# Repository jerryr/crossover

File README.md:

## Active Audio crossover
This circuit is based on https://sound-au.com/project09.htm

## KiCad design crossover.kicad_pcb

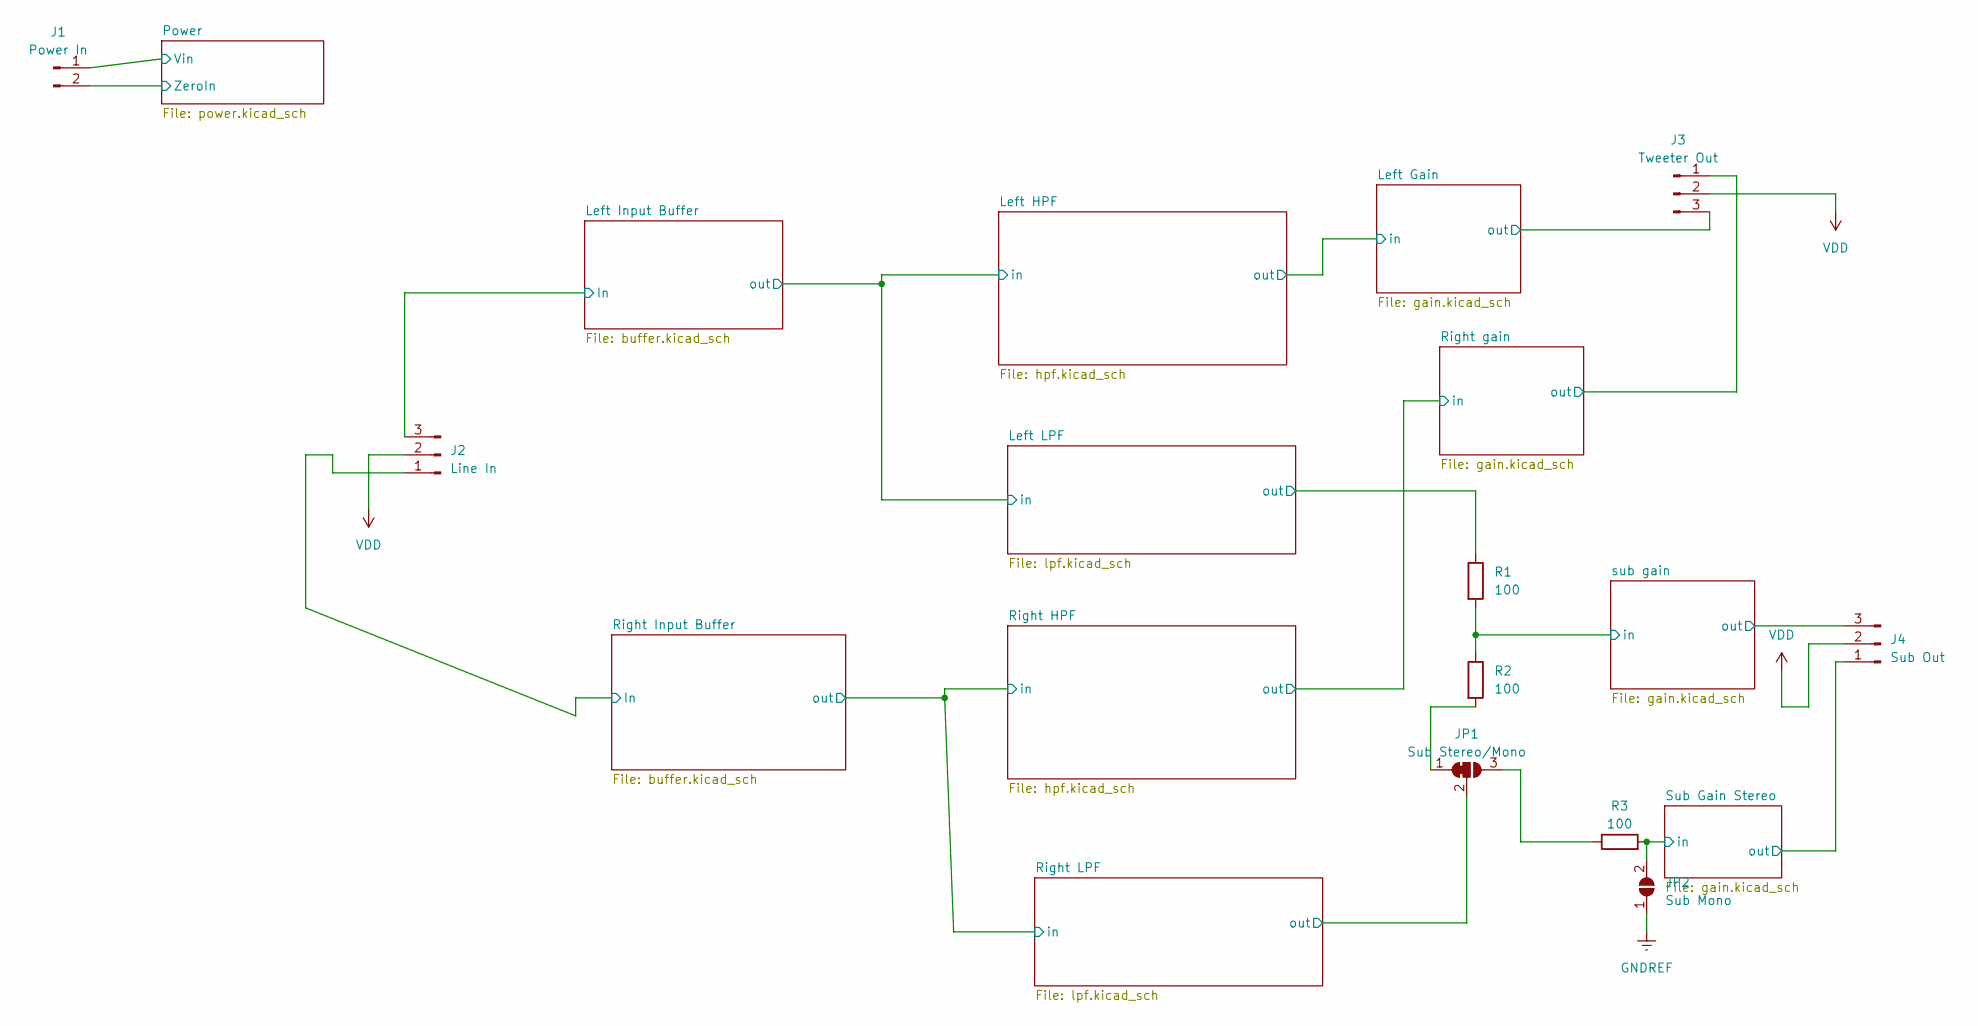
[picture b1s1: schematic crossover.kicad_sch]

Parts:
J1: Power In; JST_EH_B2B-EH-A_1x02_P2.50mm_Vertical
J2: Line In; JST_EH_B3B-EH-A_1x03_P2.50mm_Vertical
J3: Tweeter Out; JST_EH_B3B-EH-A_1x03_P2.50mm_Vertical
J4: Sub Out; JST_EH_B3B-EH-A_1x03_P2.50mm_Vertical
JP1: Sub Stereo/Mono; SolderJumper-3_P1.3mm_Open_RoundedPad1.0x1.5mm
JP2: Sub Mono; SolderJumper-2_P1.3mm_Open_RoundedPad1.0x1.5mm
R1, R2, R3: 100; R_Axial_DIN0207_L6.3mm_D2.5mm_P7.62mm_Horizontal

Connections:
/Left Gain/out: J3.3; also elsewhere on the board
/Left Input Buffer/In: J2.3; also elsewhere on the board
/Left LPF/out: R1.1; also elsewhere on the board
/Power/Vin: J1.1; also elsewhere on the board
/Right Input Buffer/In: J2.1; also elsewhere on the board
/Right LPF/out: JP1.2 (C); also elsewhere on the board
/Right gain/out: J3.1; also elsewhere on the board
/Sub Gain Stereo/in: JP2.2 (B), R3.2; also elsewhere on the board
/Sub Gain Stereo/out: J4.1; also elsewhere on the board
/sub gain/in: R1.2, R2.1; also elsewhere on the board
/sub gain/out: J4.3; also elsewhere on the board
GNDREF: JP2.1 (A); also elsewhere on the board
unnamed: JP1.1 (A), R2.2
unnamed: JP1.3 (B), R3.1
VDD: J1.2, J2.2, J3.2, J4.2; also elsewhere on the board

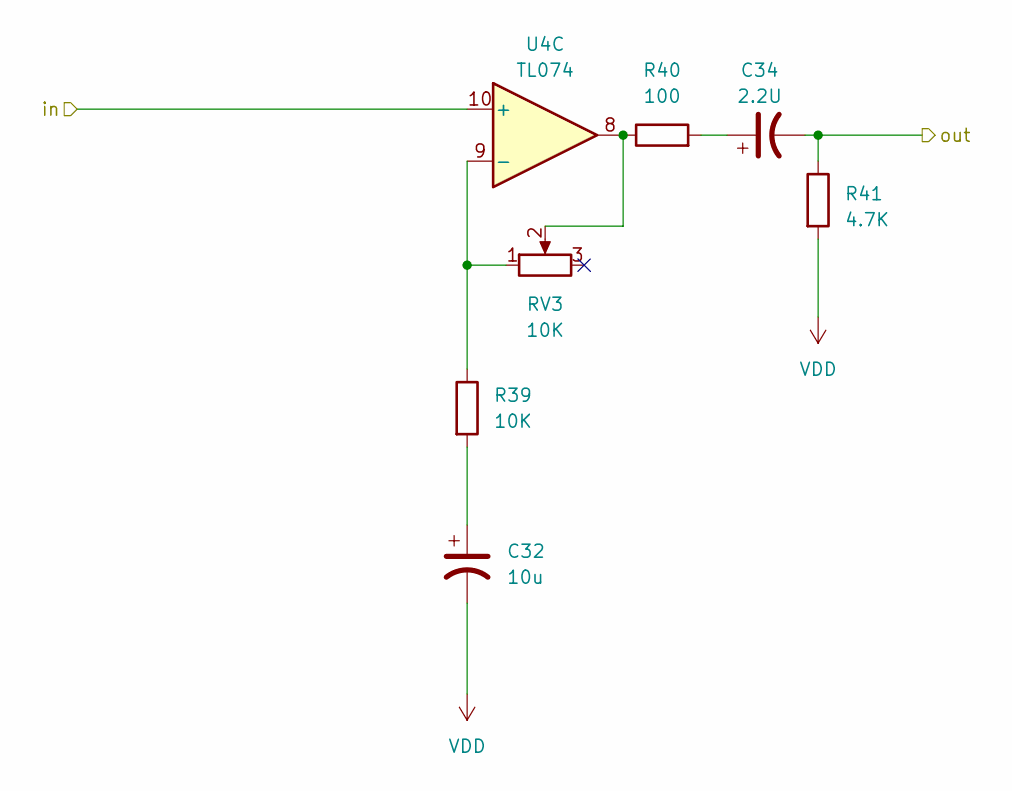
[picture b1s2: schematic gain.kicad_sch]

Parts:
C32: 10u; CP_Radial_D5.0mm_P2.50mm
C34: 2.2U; CP_Radial_D5.0mm_P2.50mm
R39: 10K; R_1206_3216Metric_Pad1.30x1.75mm_HandSolder
R40: 100; R_Axial_DIN0207_L6.3mm_D2.5mm_P7.62mm_Horizontal
R41: 4.7K; R_1210_3225Metric_Pad1.30x2.65mm_HandSolder
RV3: 10K; Potentiometer_Bourns_3386C_Horizontal
U4: TL074; SOIC-14_3.9x8.7mm_P1.27mm

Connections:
/Left Gain/in: U4.10 (+); also elsewhere on the board
/Left Gain/out: C34.2, R41.1; also elsewhere on the board
/Right HPF/out: U4.5 (+); also elsewhere on the board
/Sub Gain Stereo/in: U4.12 (+); also elsewhere on the board
/sub gain/in: U4.3 (+); also elsewhere on the board
unnamed: C32.1, R39.2
unnamed: C34.1, R40.2
unnamed 41: U4.1; also elsewhere on the board
unnamed 42: U4.7; also elsewhere on the board
unnamed: R40.1, RV3.2, U4.8
unnamed 44: U4.14; also elsewhere on the board
unnamed 55: U4.2 (-); also elsewhere on the board
unnamed 56: U4.6 (-); also elsewhere on the board
unnamed: R39.1, RV3.1, U4.9 (-)
unnamed 58: U4.13 (-); also elsewhere on the board
VDD: C32.2, R41.2; also elsewhere on the board

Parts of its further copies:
C21, C33, C35: 2.2U; CP_Radial_D5.0mm_P2.50mm
C24, C30, C36: 10u; CP_Radial_D5.0mm_P2.50mm
R27, R35, R43: 10K; R_1206_3216Metric_Pad1.30x1.75mm_HandSolder
R28, R36, R44: 100; R_Axial_DIN0207_L6.3mm_D2.5mm_P7.62mm_Horizontal
R29, R37, R45: 4.7K; R_1210_3225Metric_Pad1.30x2.65mm_HandSolder
RV1, RV2, RV4: 10K; Potentiometer_Bourns_3386C_Horizontal

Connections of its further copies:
/Right gain/out: C33.2, R37.1; also elsewhere on the board
/Sub Gain Stereo/out: C35.2, R45.1; also elsewhere on the board
/sub gain/out: C21.2, R29.1; also elsewhere on the board
unnamed: C21.1, R28.2
unnamed: C24.1, R27.2
unnamed: C30.1, R35.2
unnamed: C33.1, R36.2
unnamed: C35.1, R44.2
unnamed: C36.1, R43.2
unnamed 41: R28.1, RV1.2; also elsewhere on the board
unnamed 42: R36.1, RV2.2; also elsewhere on the board
unnamed 44: R44.1, RV4.2; also elsewhere on the board
unnamed 55: R27.1, RV1.1; also elsewhere on the board
unnamed 56: R35.1, RV2.1; also elsewhere on the board
unnamed 58: R43.1, RV4.1; also elsewhere on the board
VDD: C24.2, C30.2, C36.2, R29.2, R37.2, R45.2; also elsewhere on the board

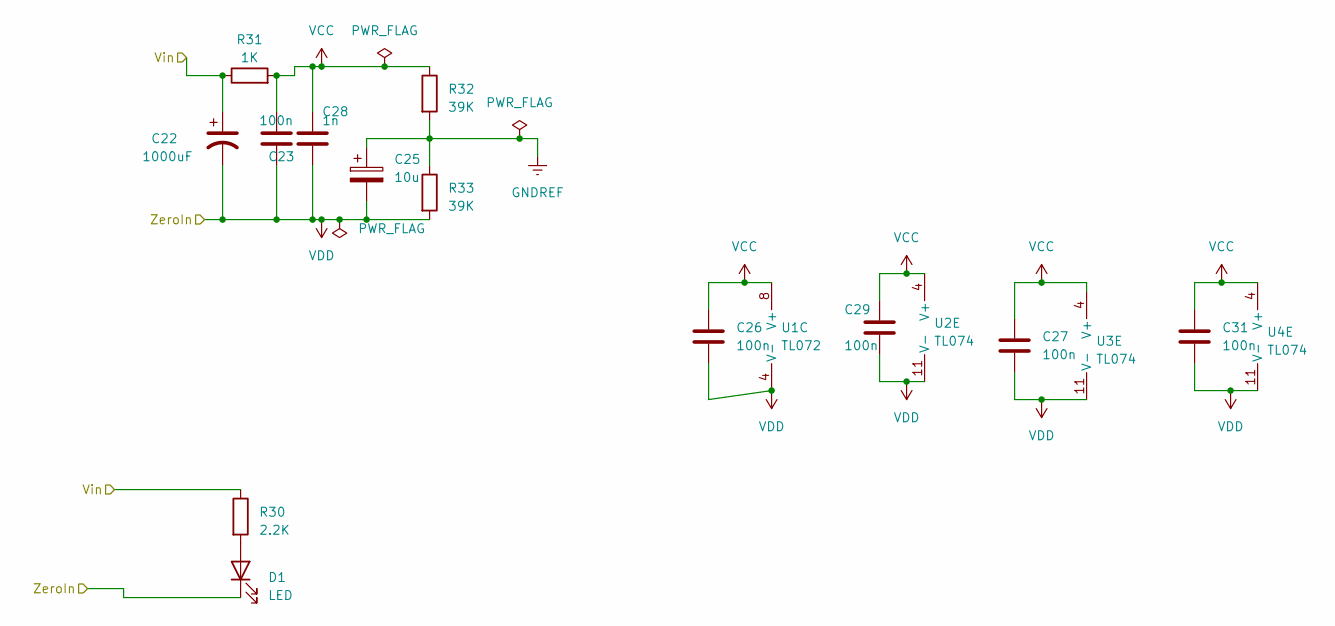
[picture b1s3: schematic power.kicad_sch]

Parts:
C22: 1000uF; CP_Radial_D10.0mm_P5.00mm
C23, C26, C27, C29, C31: 100n; C_0805_2012Metric_Pad1.18x1.45mm_HandSolder
C25: 10u; CP_Radial_D5.0mm_P2.50mm
C28: 1n; C_0805_2012Metric_Pad1.18x1.45mm_HandSolder
D1: LED; LED_1210_3225Metric_Pad1.42x2.65mm_HandSolder
R30: 2.2K; R_1210_3225Metric_Pad1.30x2.65mm_HandSolder
R31: 1K; R_1206_3216Metric_Pad1.30x1.75mm_HandSolder
R32, R33: 39K; R_1206_3216Metric_Pad1.30x1.75mm_HandSolder
U1: TL072; DIP-8_W7.62mm_Socket
U2, U3, U4: TL074; SOIC-14_3.9x8.7mm_P1.27mm

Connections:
/Left Gain/in: U2.6 (-), U2.7; also elsewhere on the board
/Left LPF/out: U2.13 (-), U2.14; also elsewhere on the board
/Power/Vin: C22.1, R30.1, R31.1; also elsewhere on the board
/Right HPF/in: U1.6 (-), U1.7; also elsewhere on the board
/Right HPF/out: U3.6 (-), U3.7, U4.5 (+); also elsewhere on the board
/Right LPF/out: U3.13 (-), U3.14; also elsewhere on the board
/Sub Gain Stereo/in: U4.12 (+); also elsewhere on the board
/sub gain/in: U4.3 (+); also elsewhere on the board
GNDREF: C25.1, R32.2, R33.1; also elsewhere on the board
unnamed: D1.2 (A), R30.2
unnamed 41: U4.1; also elsewhere on the board
unnamed 42: U4.7; also elsewhere on the board
unnamed 44: U4.14; also elsewhere on the board
unnamed 46: U1.5 (+); also elsewhere on the board
unnamed 48: U2.5 (+); also elsewhere on the board
unnamed 50: U2.12 (+); also elsewhere on the board
unnamed 52: U3.5 (+); also elsewhere on the board
unnamed 54: U3.12 (+); also elsewhere on the board
unnamed 55: U4.2 (-); also elsewhere on the board
unnamed 56: U4.6 (-); also elsewhere on the board
unnamed 58: U4.13 (-); also elsewhere on the board
VCC: C23.1, C26.1, C27.1, C28.1, C29.1, C31.1, R31.2, R32.1, U1.8 (V+), U2.4 (V+), U3.4 (V+), U4.4 (V+)
VDD: C22.2, C23.2, C25.2, C26.2, C27.2, C28.2, C29.2, C31.2, D1.1 (K), R33.2, U1.4 (V-), U2.11 (V-), U3.11 (V-), U4.11 (V-); also elsewhere on the board

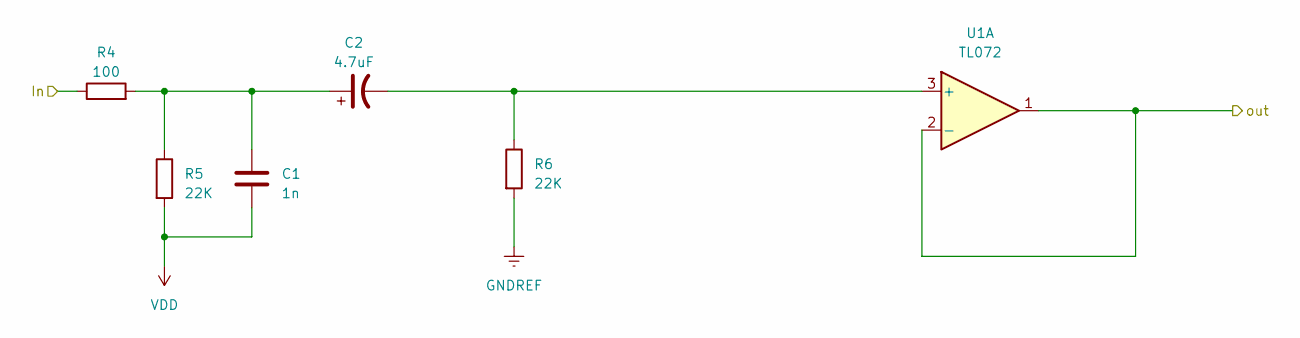
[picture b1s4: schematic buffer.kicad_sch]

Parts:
C1: 1n; C_0805_2012Metric_Pad1.18x1.45mm_HandSolder
C2: 4.7uF; CP_Radial_D5.0mm_P2.00mm
R4: 100; R_Axial_DIN0207_L6.3mm_D2.5mm_P7.62mm_Horizontal
R5, R6: 22K; R_1206_3216Metric_Pad1.30x1.75mm_HandSolder
U1: TL072; DIP-8_W7.62mm_Socket

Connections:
/Left HPF/in: U1.1, U1.2 (-); also elsewhere on the board
/Left Input Buffer/In: R4.1; also elsewhere on the board
/Right HPF/in: U1.6 (-), U1.7; also elsewhere on the board
GNDREF: R6.2; also elsewhere on the board
unnamed: C1.1, C2.1, R4.2, R5.1
unnamed: C2.2, R6.1, U1.3 (+)
unnamed 46: U1.5 (+); also elsewhere on the board
VDD: C1.2, R5.2; also elsewhere on the board

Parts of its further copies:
C3: 1n; C_0805_2012Metric_Pad1.18x1.45mm_HandSolder
C4: 4.7uF; CP_Radial_D5.0mm_P2.00mm
R7: 100; R_Axial_DIN0207_L6.3mm_D2.5mm_P7.62mm_Horizontal
R8, R9: 22K; R_1206_3216Metric_Pad1.30x1.75mm_HandSolder

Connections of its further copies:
/Right Input Buffer/In: R7.1; also elsewhere on the board
GNDREF: R9.2; also elsewhere on the board
unnamed: C3.1, C4.1, R7.2, R8.1
unnamed 46: C4.2, R9.1; also elsewhere on the board
VDD: C3.2, R8.2; also elsewhere on the board

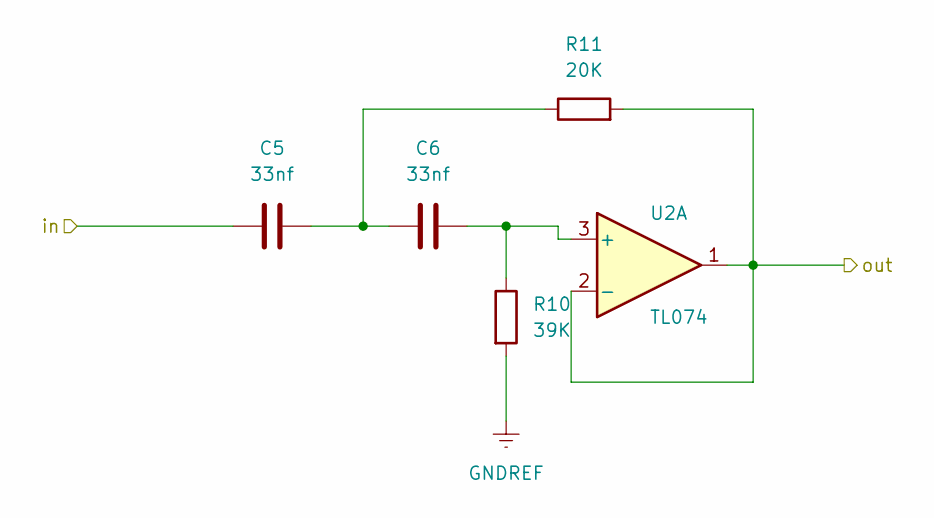
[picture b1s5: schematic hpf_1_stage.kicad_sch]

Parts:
C5, C6: 33nf; C_Disc_D6.0mm_W2.5mm_P5.00mm
R10: 39K; R_1206_3216Metric_Pad1.30x1.75mm_HandSolder
R11: 20K; R_1206_3216Metric_Pad1.30x1.75mm_HandSolder
U2: TL074; SOIC-14_3.9x8.7mm_P1.27mm

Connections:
/Left Gain/in: U2.6 (-), U2.7; also elsewhere on the board
/Left HPF/HPF Stage 2/in: R11.2, U2.1, U2.2 (-); also elsewhere on the board
/Left HPF/in: C5.1; also elsewhere on the board
/Left LPF/out: U2.13 (-), U2.14; also elsewhere on the board
GNDREF: R10.2; also elsewhere on the board
unnamed: C5.2, C6.1, R11.1
unnamed: C6.2, R10.1, U2.3 (+)
unnamed 48: U2.5 (+); also elsewhere on the board
unnamed 50: U2.12 (+); also elsewhere on the board

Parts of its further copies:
C7, C8, C9, C10, C11, C12: 33nf; C_Disc_D6.0mm_W2.5mm_P5.00mm
R12, R14, R16: 39K; R_1206_3216Metric_Pad1.30x1.75mm_HandSolder
R13, R15, R17: 20K; R_1206_3216Metric_Pad1.30x1.75mm_HandSolder

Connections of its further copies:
/Left Gain/in: R13.2; also elsewhere on the board
/Left HPF/HPF Stage 2/in: C7.1; also elsewhere on the board
/Right HPF/HPF Stage 2/in: C11.1, R15.2; also elsewhere on the board
/Right HPF/in: C9.1; also elsewhere on the board
/Right HPF/out: R17.2; also elsewhere on the board
GNDREF: R12.2, R14.2, R16.2; also elsewhere on the board
unnamed: C7.2, C8.1, R13.1
unnamed: C9.2, C10.1, R15.1
unnamed: C11.2, C12.1, R17.1
unnamed 48: C8.2, R12.1; also elsewhere on the board
unnamed 51: C10.2, R14.1; also elsewhere on the board
unnamed 52: C12.2, R16.1; also elsewhere on the board

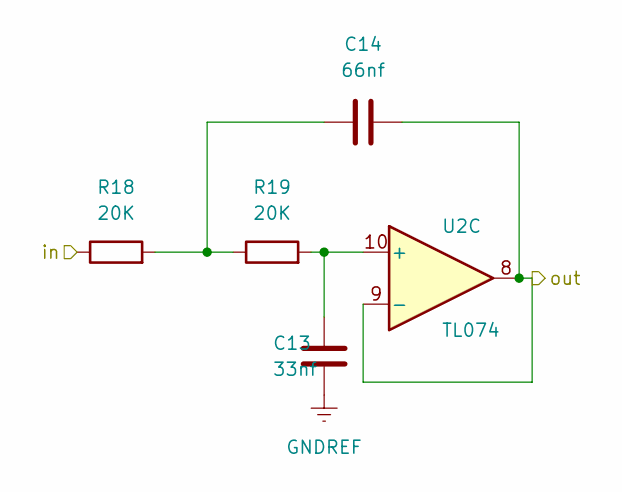
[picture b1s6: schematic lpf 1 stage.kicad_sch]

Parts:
C13: 33nf; C_Disc_D6.0mm_W2.5mm_P5.00mm
C14: 66nf; C_Disc_D6.0mm_W2.5mm_P5.00mm
R18, R19: 20K; R_1206_3216Metric_Pad1.30x1.75mm_HandSolder
U2: TL074; SOIC-14_3.9x8.7mm_P1.27mm

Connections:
/Left Gain/in: U2.6 (-), U2.7; also elsewhere on the board
/Left HPF/in: R18.1; also elsewhere on the board
/Left LPF/LPF Stage 1/out: C14.2, U2.8, U2.9 (-); also elsewhere on the board
/Left LPF/out: U2.13 (-), U2.14; also elsewhere on the board
GNDREF: C13.1; also elsewhere on the board
unnamed: C14.1, R18.2, R19.1
unnamed 48: U2.5 (+); also elsewhere on the board
unnamed: C13.2, R19.2, U2.10 (+)
unnamed 50: U2.12 (+); also elsewhere on the board

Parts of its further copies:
C15, C17, C19: 33nf; C_Disc_D6.0mm_W2.5mm_P5.00mm
C16, C18, C20: 66nf; C_Disc_D6.0mm_W2.5mm_P5.00mm
R20, R21, R22, R23, R24, R25: 20K; R_1206_3216Metric_Pad1.30x1.75mm_HandSolder

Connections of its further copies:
/Left LPF/LPF Stage 1/out: R20.1; also elsewhere on the board
/Left LPF/out: C16.2; also elsewhere on the board
/Right HPF/in: R22.1; also elsewhere on the board
/Right LPF/LPF Stage 1/out: C18.2, R24.1; also elsewhere on the board
/Right LPF/out: C20.2; also elsewhere on the board
GNDREF: C15.1, C17.1, C19.1; also elsewhere on the board
unnamed: C16.1, R20.2, R21.1
unnamed: C18.1, R22.2, R23.1
unnamed: C20.1, R24.2, R25.1
unnamed 50: C15.2, R21.2; also elsewhere on the board
unnamed 53: C17.2, R23.2; also elsewhere on the board
unnamed 54: C19.2, R25.2; also elsewhere on the board

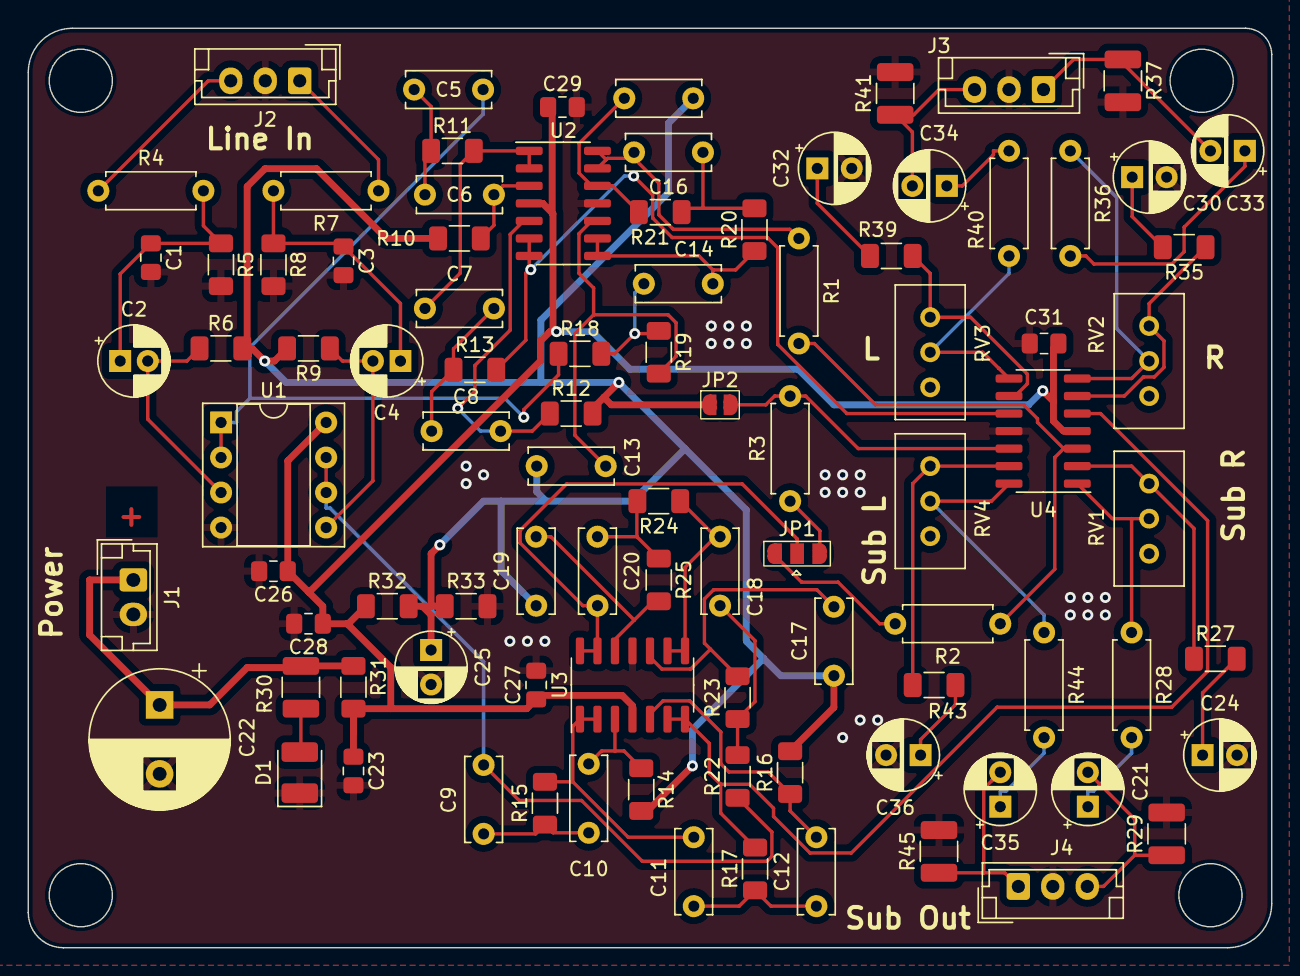
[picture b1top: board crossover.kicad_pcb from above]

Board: 2 copper layers, 90.2 x 66.7 mm, 92 parts (0 on the bottom side), 61 nets.

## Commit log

2023-02-18 Set boundaries, labels
2023-02-18 Fully routed
2023-05-04 Final PCB Layout
2023-05-04 Added readme
2023-05-05 Update to KiCad 7
2023-05-07 Improve power supply decoupling, add LED indicator
2023-05-07 Fix gitignore
2023-05-07 Fix input section
2023-05-07 Fix output filters
2023-05-08 Allow stereo/mono switching for Sub
2023-05-08 Re-annotate and run erc
2023-05-09 Fix some ERC warnings
2023-05-09 Switch to TL074
2023-05-09 Assign footprints to everything
2023-05-13 Finish placing
2023-05-28 fix gain stage for DC offset and some changes to power filtration
2023-08-13 Finished routing
